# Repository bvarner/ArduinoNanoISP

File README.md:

# ArduinoNanoISP
An Arduino Nano as an ISP for burning bootloaders on other Arduinos.

This is a pretty simple KiCad design, with very forgiving trace sizes and tolerances.

You should be able to hot-iron transfer this design (assuming you get rid of the fill zones and make actual net routes for the GND).
In my own case, I used my Varnerized ANT CNC machine to mill a board, which took about 1:20 minutes and had a single tool change, thanks to the massive 0.8mm holes used throughout the design.

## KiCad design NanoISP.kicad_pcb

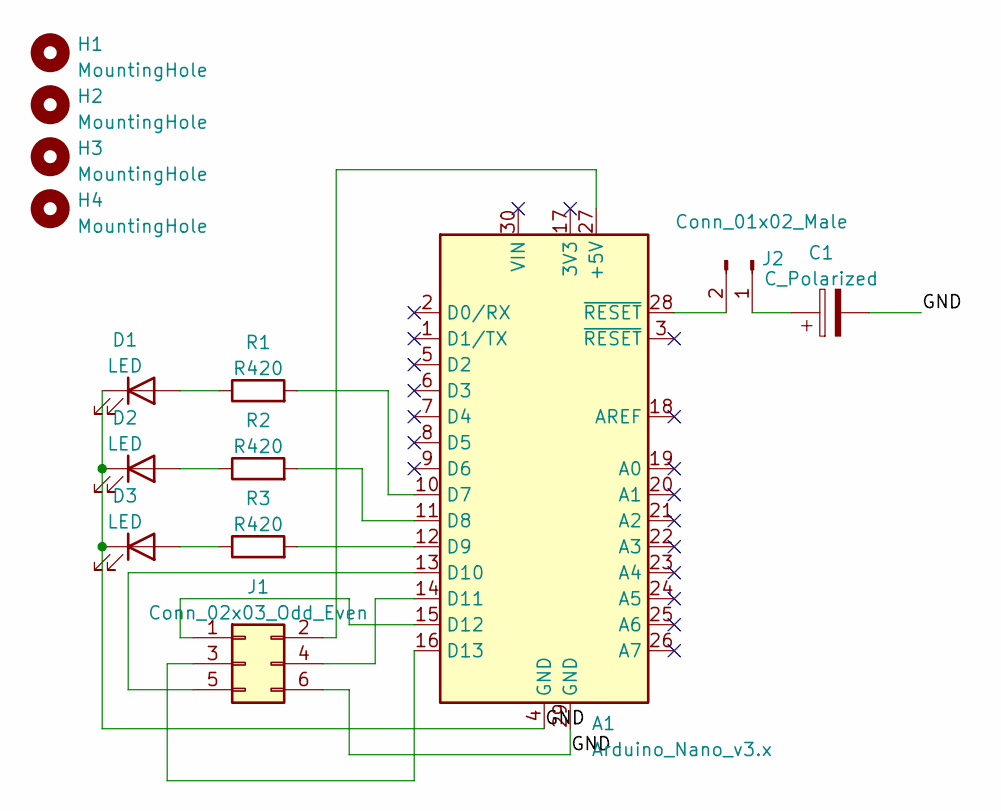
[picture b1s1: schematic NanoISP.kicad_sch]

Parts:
A1: Arduino_Nano_v3.x; Arduino_Nano
C1: C_Polarized; CP_Radial_D5.0mm_P2.50mm
D1, D2, D3: LED; LED_D5.0mm
H1, H2, H3, H4: MountingHole; MountingHole_2.2mm_M2_DIN965
J1: Conn_02x03_Odd_Even; PinHeader_2x03_P2.54mm_Vertical
J2: Conn_01x02_Male; PinHeader_1x02_P2.54mm_Vertical
R1, R2, R3: R420; R_Axial_DIN0207_L6.3mm_D2.5mm_P7.62mm_Horizontal

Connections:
/GND: A1.4 (GND), A1.29 (GND), C1.2, D1.1 (K), D2.1 (K), D3.1 (K), J1.6
unnamed: A1.10 (D7), R1.2
unnamed: A1.11 (D8), R2.2
unnamed: A1.12 (D9), R3.2
unnamed: A1.13 (D10), J1.5
unnamed: A1.14 (D11), J1.4
unnamed: A1.15 (D12), J1.1
unnamed: A1.16 (D13), J1.3
unnamed: A1.27 (+5V), J1.2
unnamed: A1.28 (~RESET), J2.2
unnamed: C1.1, J2.1
unnamed: D1.2 (A), R1.1
unnamed: D2.2 (A), R2.1
unnamed: D3.2 (A), R3.1

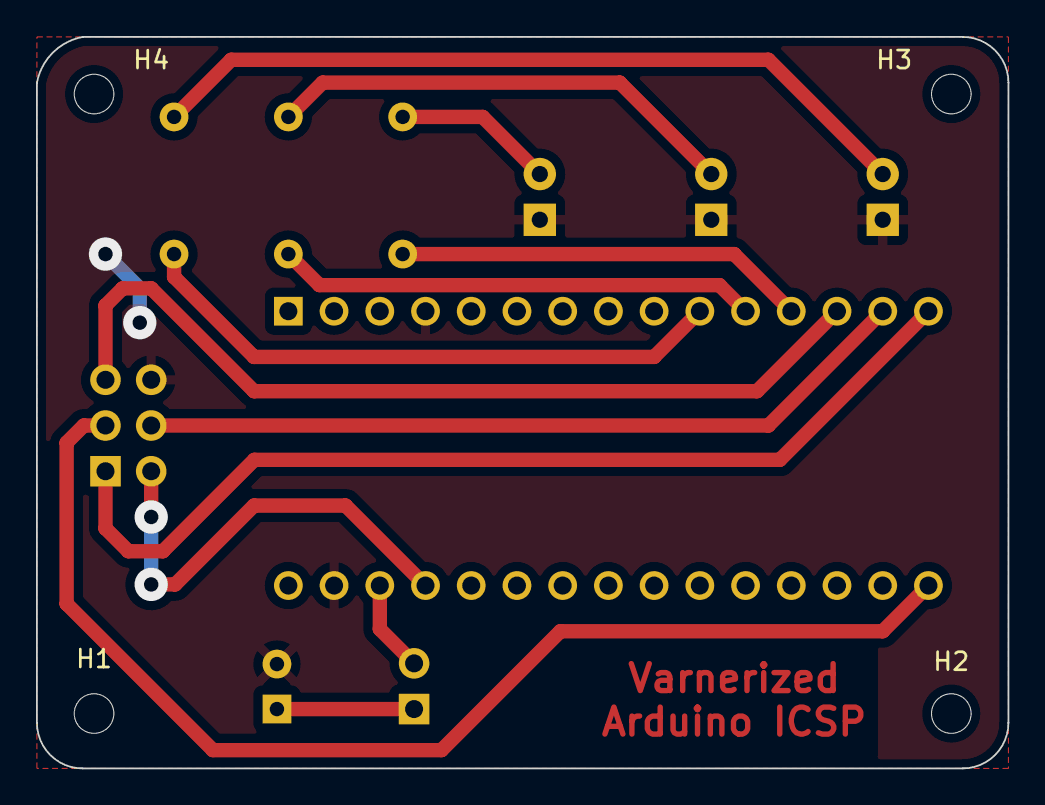
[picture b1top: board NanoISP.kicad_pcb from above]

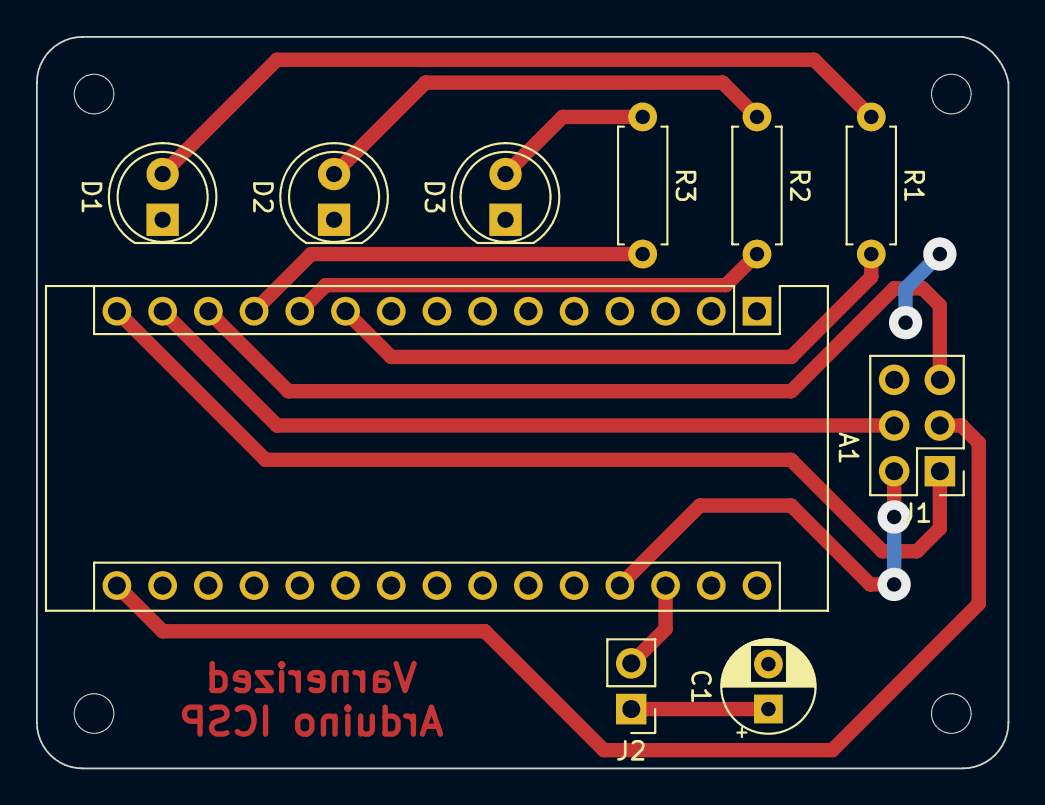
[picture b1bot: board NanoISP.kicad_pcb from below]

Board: 2 copper layers, 54.0 x 40.6 mm, 14 parts (10 on the bottom side), 14 nets.

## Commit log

2022-06-14 Initial checking of the kicad project.
2022-06-14 Add the plots.
2022-06-14 No more DRC issues. Wider via.
2022-06-14 Inverse plot.
2022-06-24 Added the capacitor for handling ready / unready.
2022-06-25 Updates with dimensions.
2022-06-25 Readme.
2022-06-25 Fixed a small bug.
